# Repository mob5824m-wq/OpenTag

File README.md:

# OpenTag

OpenTag is an independent, open-source NFC handheld. `device/` contains the
ESP32-S3 firmware; `hardware/` contains the carrier PCB, enclosure CAD, wiring
guide, and parts list.

> OpenTag is not affiliated with or endorsed by Nintendo or any tag/device
> manufacturer. Amiibo is a trademark of Nintendo. **All amiibo tag data is
> user-supplied** — the project bundles, generates, and distributes none of
> it. Upload backups of tags you own, and only write to tags you are
> authorized to program.

## What it does

- **Write NDEF notes** — sync a text or HTTP(S) URL note over BLE and write it
  to a real NTAG215 (verified by read-back), from the device menu.
- **Emulate the NDEF note** — present the note as a virtual, read-only
  NTAG215; phones read it like any NDEF tag.
- **Amiibo library** — upload a `.zip` of your own NTAG215 `.bin` dumps
  through the web page or the **Android app**, browse them on the OLED, and
  tap a console with the dump's own 7-byte UID presented by the NFC emulator.
  **OpenTag emulates amiibo — that's the product**; bins show metadata and
  box art in the web page and app, matched by file name against a bundled
  932-entry amiibo database.
- **Android app** ([`android-app/`](android-app/)) — native Kotlin app
  (no dependencies) for BLE file dumping: pick `.bin` dumps or a `.zip` of
  them, upload to the device, browse the on-device library, and trigger
  emulation. Every merge to `main` auto-builds a fresh signed `.apk`
  (`app-v*` releases on the Releases page) — download and sideload it, no
  Android Studio needed.
- **OpenTag Mini** — a screenless, pocket-flatter variant of the same
  electronics: no OLED, no nav buttons, **no Bluetooth pairing PIN**
  (just-works pairing — it's keyed to your desk, not to a shared bench).
  Everything is driven from the Android app or the web page, which
  recognise the device and label it **Mini** with a matching button set;
  the single button handles battery chirps, travel mode and power.
- **Wireless charging (optional)** — a Qi receiver coil inside the back
  plate charges the OpenTag from any Qi pad through the existing TP4056
  (an engraved ring on the back marks the spot); with the optional charge
  -sense wire, a bolt icon on the OLED confirms the pad is coupled.
- **Tag backup (reader mode)** — from the device menu, tap any amiibo
  against the back window and the firmware reads, validates, and stores the
  dump in the library (named by the tag's UID; full 1024-byte images for
  V3/NTAG I²C tags). No phone needed.
- **Tag inspector** — the third menu item turns the OpenTag into a tag
  identifier: tap any tag on the back window and the OLED shows its UID,
  chip type (NTAG213/215/216, MIFARE UL…) and any NDEF text/URL payload.
  Nothing is written; it's the safe "what is this tag?" answer.
- **Battery gauge + low-battery protection (optional)** — a 100k/100k
  divider on B+ feeds GPIO4; the header shows a charge percentage, turns
  red at/below 15 %, warns once at 3.35 V and (with the divider fitted)
  powers the device off cleanly if the cell sags below 3.25 V for 30 s.
- **BLE pairing with a PIN** — the first phone to connect runs the standard
  numeric-comparison pairing flow: the OLED shows a random 6-digit code,
  the phone asks to confirm it, and the bond is stored (a failed exchange
  is disconnected immediately). Re-pair by deleting the bond on the phone.
- **USB drive mode (read-only)** — docked in the menu, the DevKit's USB-C
  port enumerates as a USB mass-storage drive exposing a read-only snapshot
  of the amiibo library (plus a README) — drag bins off the device with no
  app at all. Loading new dumps still goes over BLE (the drive is a
  snapshot; OK/BACK ejects it).
- **Wi-Fi OTA updates (optional)** — provision Wi-Fi credentials over BLE
  (`WIFI:<ssid>|<pass>`), then trigger an update from the web page's
  Settings (or `OTA:START`): the device fetches the latest GitHub release,
  flashes only the app partition and reboots — library and settings survive,
  exactly like the wired one-command updater.
- **Piezo feedback (optional)** — a passive buzzer on GPIO5 chirps on tag
  backup, verified writes, pairing and the low-battery warning. Unwired,
  the device stays silent, as before.
- **One-command firmware updates** ([`tools/update_opentag.py`](tools/update_opentag.py))
  — plug the OpenTag into a computer and run the script: it downloads the
  latest firmware release from GitHub (CI builds and attaches it on every
  `v*` tag) and flashes **only the app partition** — your amiibo library,
  settings, and note survive every update.
- **Advanced: write amiibo to physical NTAG215 tags (TagMo-style)** — with
  your own `unfixed-info.bin` / `locked-secret.bin` key files uploaded over
  BLE, the device can re-sign a dump for a blank tag's own UID, write and
  verify it, and optionally lock it (irreversible, long-press confirm on the
  device). Emulation needs none of this; the flow remains available behind a
  long-press in the device library.
- **BLE sync** — Web Bluetooth page with note management, .zip upload, device
  library listing with metadata + box art, remote emulate/delete.
- **Web preview of the device UI** ([`device/web-preview/`](device/web-preview/))
  — a browser simulation of the OLED interface (every screen, color, and
  pixel position ported from `drawScreen()`) with working buttons and
  long-press, for UI testing with no hardware attached.

## Set up your OpenTag

Three ways in, depending on what's on your desk. **A** needs nothing, **B**
is a working device on a bench in an afternoon, **C** is the finished
handheld.

### A · No hardware — try the interface (1 minute)

Open [`device/web-preview/index.html`](device/web-preview/index.html) in any
browser: a pixel-faithful simulation of the OLED menu with working buttons
and long-press — every screen the real device shows, nothing to install.

### B · Bench build — a working device today

Parts: **ESP32-S3-DevKitC-1** (16 MB flash), **PN532Killer**, **1.3"
SSD1351 OLED** (7-pin SPI), 4 × tactile buttons, Dupont jumpers, USB-C
cable. No PCB, no soldering — USB powers the whole bench setup.

1. Install [PlatformIO](https://platformio.org/) (VS Code extension or
   `pip install platformio`).
2. Flash the firmware and the library filesystem:
   ```sh
   cd device
   pio run -e opentag_s3 -t upload      # firmware (app partition only)
   pio run -e opentag_s3 -t uploadfs    # LittleFS: on-device amiibo storage
   ```
3. Wire the modules (full map and rationale in
   [`docs/HARDWARE.md`](docs/HARDWARE.md)):

   | Connection | DevKit pin (GPIO) | Module side |
   |---|---|---|
   | OLED VCC / GND | J1-1 (3V3) / GND | VCC / GND |
   | OLED SCK / MOSI | J1-18 (12) / J1-17 (11) | SCL / SDA |
   | OLED CS / DC / RST | J1-16 (10) / J1-15 (9) / J1-12 (8) | CS / DC / RES |
   | Killer 3V3 / GND (J4) | J1-2 (3V3) / GND | VCC / GND |
   | Killer RX / TX (J4) | J1-10 TX (17) / J1-11 RX (18) | crossed: TX → RX |
   | Buttons UP / DOWN / OK / BACK | J3-6 (42) / J3-5 (2) / J3-4 (1) / J1-19 (13) | one leg each; other legs to GND |

4. Plug in USB — the OLED shows the menu within a couple of seconds. Only
   the NFC actions need the Killer attached; trying one without it shows
   **PN532Killer absent** on screen. Wire it in and the whole menu is live.
5. Serve the sync page. Web Bluetooth only runs on a secure origin
   (localhost or HTTPS) — **double-clicking the file is not enough**:
   ```sh
   cd device/web-sync
   python3 -m http.server 8000        # then open http://localhost:8000
   ```
6. In Chrome or Edge: **Connect over BLE** (the device shows up as
   *OpenTag*) → pick a `.zip` of your own NTAG215 `.bin` dumps → they land
   in the on-device library with names and box art. Browse on the OLED,
   press OK on one, and tap your console.

Optional extras on the same hardware: send a text/URL **NDEF note** from the
sync page (the device menu can write it to a blank NTAG215 or emulate it —
a good first test of the tag pipeline), and — only if you write amiibo to
physical tags — upload your `unfixed-info.bin` / `locked-secret.bin` key
files. Emulation needs neither.

### C · Full handheld

1. **Order the PCB** — upload
   [`hardware/pcb/gerbers/opentag-gerbers.zip`](hardware/pcb/gerbers/) to any
   fab (JLCPCB, PCBWay, …). The zip is complete and machine-verified by its
   generator.
2. **Print the shell** — [`hardware/cad/stl/`](hardware/cad/stl/): front
   shell, back plate, 4 button caps (PLA/PETG, no supports needed).
3. **Assemble** per [`docs/WIRING.md`](docs/WIRING.md);
   parts and budget in [`docs/BOM.md`](docs/BOM.md) (≈ $72–102
   complete). Print [`docs/opentag-user-guide.pdf`](docs/opentag-user-guide.pdf)
   as the user manual.
4. The device is identical to the bench build — continue from step 5 in
   path **B**.

Updating an assembled device later never touches your library:
`python tools/update_opentag.py` flashes only the app partition
([details](#updating-the-firmware-keeps-your-amiibos)).

### D · OpenTag Mini (screenless)

The same electronics and BLE protocol with the screen and nav buttons
removed: **one button, a chirp, and the app or web page for everything.**
No OLED, no carrier PCB — the DevKitC and the three modules mount straight
into printed trays, and the shell closes at 83.6 × 93.6 × 16.3 mm
(31 % shorter and 44 % thinner than the handheld, and it skips the numeric
pairing PIN entirely). The Android app and web page detect it on connect
(`INFO` → `mini`) and swap in the Mini control set — emulate, backup,
inspect, write note — same library, same keys, same Wi-Fi/OTA.

1. **Print the Mini shell** —
   [`hardware/cad/stl/opentag_mini_*.stl`](hardware/cad/stl/): front
   shell, back plate, **1** button cap (no desk stand — the Mini has no
   reading pose to hold).
2. **Assemble point-to-point** per
   [`docs/WIRING.md`](docs/WIRING.md#opentag-mini-variant) — no PCB, no
   soldering beyond tinning the module pads: DevKitC + Killer + TP4056 +
   MT3608 + LiPo + one tactile switch, parts in
   [`docs/BOM.md`](docs/BOM.md#opentag-mini-delta).
3. **Flash the Mini firmware** (same library filesystem as the handheld):
   ```sh
   cd device
   pio run -e opentag_mini -t upload
   pio run -e opentag_mini -t uploadfs
   ```
4. Pair from the app or web page — the device shows up as **OpenTag Mini**
   and connects with no PIN prompt. The single button: **short press**
   chirps the battery level (one chirp per 20 %), **triple press** toggles
   travel mode, **hold 1.5 s** powers off (short press wakes).

ESP32-S3-DevKitC-1 + **PN532Killer** (ST25R3916-class NFC emulator; the
classic PN532 cannot present the 7-byte, signature-bound UIDs amiibo relies
on) + SSD1351 OLED + four buttons (UP / DOWN / OK / BACK) + LiPo power
(TP4056 + MT3608). The NFC
board talks HSU UART to the ESP32; a 540-byte page image per tag is all the
firmware pushes. The SW-corner tab is a lanyard / keyring loop (4.2 mm bore,
continuous through the front/back seam). See [`docs/HARDWARE.md`](docs/HARDWARE.md) for the full
interface map and [`hardware/`](hardware/) for:

| File | Contents |
|---|---|
| `hardware/pcb/opentag-carrier.kicad_pcb` | 90 × 60 mm 2-layer carrier, all through-hole |
| `hardware/pcb/generate_carrier_pcb.py` | Regenerates the PCB and self-checks connectivity + clearance |
| `hardware/pcb/gerbers/` | Fab-ready Gerber set + Excellon drill + `opentag-gerbers.zip` — the generator writes them and re-parses them to verify against the model |
| `docs/WIRING.md` | Assembly, power chain, signal map, bring-up |
| `docs/HARDWARE.md` | Device interface baseline — the contract the firmware implements (buttons, display, NFC, power, USB) |
| `hardware/cad/opentag_shell.cad` | Parametric 2-part handheld shell + button caps, with the ⚡-marked USB-C charge port on the west wall and a lanyard loop tab on the SW corner (OpenSCAD source; `.cad` is the project's extension) |
| `hardware/cad/opentag_mini_shell.cad` | Parametric 2-part **Mini** shell + its single button cap — screenless variant, 83.6 × 93.6 × 16.3 mm, module trays instead of a carrier PCB, same west USB / east charge-slot layout and lanyard loop |
| `hardware/cad/stl/*.stl` | Print-ready binary STLs: handheld front shell, back plate, button cap (print 4) and optional desk stand; Mini front shell, back plate, button cap (print 1) |
| `tools/cad_to_stl.py` | Regenerates the STLs from the `.cad` without OpenSCAD (`pip install trimesh manifold3d scipy rtree`) and self-checks watertightness, features and front/back fit |
| `tools/cad_mini_to_stl.py` | Same idea for the Mini shell: parses `opentag_mini_shell.cad`, rebuilds all three parts, and self-checks volumes, features and front/back fit || `docs/BOM.md` | Parts list and budget (≈ $72–102) |
| `docs/opentag-user-guide.pdf` | The printed instruction booklet — 16 A5 pages covering charging, the desk stand, buttons, the library, V3 amiibo, BLE sync, writes, USB drive, the Mini variant and troubleshooting |
| `docs/ANDROID-APP.md` | Android companion app — features, BLE protocol, releases |
| `docs/SIGNING-KEY.md` | The committed APK signing key: why it's public, and how to swap in a private one |
| `tools/make_booklet.py` | Regenerates the booklet (`pip install fpdf2`); its cover art is parsed straight from the shell's own wordmark font and bolt icon |

## Updating the firmware (keeps your amiibos)

Push a `v*` tag and CI (`.github/workflows/firmware.yml`) builds **both**
firmwares — the handheld and the Mini — and attaches them to a GitHub
release as `opentag-firmware-<tag>.bin` and
`opentag-mini-firmware-<tag>.bin`. Then, on any computer with Python:

```sh
pip install esptool
python tools/update_opentag.py            # auto port, latest release (handheld)
python tools/update_opentag.py --mini     # the Mini variant
python tools/update_opentag.py --tag v1.2 # a specific release
python tools/update_opentag.py --bin firmware.bin --port COM5
```

The script reads the app partition offset from `device/partitions_16mb.csv`
and flashes **only that partition** — the LittleFS amiibo library, NVS
settings, and pending note are never touched. If no release asset exists it
falls back to building locally with `pio run`.

## Android app

Open [`android-app/`](android-app/) in Android Studio and run — see
[`docs/ANDROID-APP.md`](docs/ANDROID-APP.md). Platform
APIs only, no dependencies; minSdk 23.

## Tests and gates (host-native, no hardware)

The firmware build commands live in [Setup B](#b--bench-build--a-working-device-today).
Everything below runs on any machine with `g++` — no toolchain download, no
device attached.

Unit tests:

```sh
cd device/test
g++ -std=c++11 -Wall -Wextra -pedantic -I ../src test_ntag215_emu.cpp -o t1 && ./t1
g++ -std=c++11 -Wall -Wextra -pedantic -I host_stubs -I ../src test_pn532_uart.cpp -o t2 && ./t2
g++ -std=c++11 -Wall -Wextra -pedantic -I ../src test_amiibo_crypto.cpp -o t3 && ./t3
```

`test_amiibo_crypto` checks the signing pipeline byte-for-byte against
fixtures generated by the real
[amiitool](https://github.com/socram8888/amiitool) (MIT): its AES-128-CTR /
HMAC-SHA256 reference backends are themselves validated against FIPS-197,
FIPS-180-4 and RFC 4231 vectors first.

A firmware compile gate (syntax/type check of both firmwares against stub
Arduino/NimBLE/mbedtls headers — no toolchain download needed):

```sh
cd device/test
g++ -std=c++11 -Wall -Wextra -fsyntax-only -I host_stubs_main -I ../src ../src/main.cpp
g++ -std=c++11 -Wall -Wextra -fsyntax-only -I host_stubs_main -I ../src ../src/mini/main.cpp
```

CI runs all of the above plus full PlatformIO builds of **both** firmwares
on every PR or push touching `device/`
([firmware.yml](.github/workflows/firmware.yml)); only `v*` tag pushes
publish releases.

## Web sync

Open `device/web-sync/index.html` from a secure origin (HTTPS or localhost)
in Chrome/Edge, connect over BLE, then:

- queue a text/URL note and send it;
- choose a `.zip`, loose `.bin` dumps, or Flipper Zero `.nfc` files of your
  NTAG215 backups — the page unzips locally with the browser's native
  `DecompressionStream`, accepts any container layout (532/540/572 B,
  zero/newline-padded, N2 Elite 32-byte header, Flipper page lists), validates
  each dump (UID BCC, NTAG215 capability container), and copies the normalized
  540-byte image to the device in BLE chunks;
- every bin — local and on-device — shows **amiibo metadata and box art**,
  matched by file name (16-hex amiibo ID first, then a fuzzy name match)
  against `device/web-sync/amiibo-db.js`, a 932-entry database generated from
  the community AmiiboAPI project. The amiibo ID inside a retail dump is
  AES-encrypted, so file names are the reliable key. Images load from
  AmiiboAPI's CDN with a colored-initial fallback offline;
- list, emulate, or delete library entries on the device — emulation is the
  point; there is no per-amiibo write button;
- (advanced) upload your **amiibo signing keys** (`unfixed-info.bin` +
  `locked-secret.bin`, or one combined 160-byte retail file) if you also use
  the device's long-press physical-tag write flow.

Nothing is uploaded to any server; all processing happens in your browser.

### Amiibo metadata database

[`amiibo.json`](amiibo.json) (repository root) is the canonical,
human-editable database — 932 entries mapping each 16-hex amiibo ID to
`[name, amiiboSeries, type, gameSeries, releaseYear]`, generated from the
community [AmiiboAPI] database. Edit it, then run:

```sh
python tools/gen_amiibo_db.py   # -> web-sync/amiibo-db.js + android assets
```

[AmiiboAPI]: https://github.com/N3evin/AmiiboAPI

## Writing an amiibo to a physical tag

The write flow is the TagMo "WRITE TAG (AUTO)" sequence, re-implemented in
portable C++ from the MIT-licensed amiitool reference:

1. Read the blank tag's pages 0–3 (UID) and check `GET_VERSION` says NTAG215
   and the static lock bytes are still clear.
2. Decrypt the stored retail dump with keys derived from its own UID, patch
   the new tag's UID + BCC bytes in, re-encrypt and re-sign both HMACs.
3. Program pages 3–129, then the PWD (133) and PACK (134) pages derived from
   the new UID.
4. Read everything back and compare; finally `PWD_AUTH` must answer with the
   written PACK.
5. Optionally lock the tag (page 2 `xx xx 0F E0`, page 130 `01 00 0F 00`,
   page 131 `00 00 00 04` = AUTH0 4, page 132 `5F 00 00 00`) — **this is
   irreversible** and always requires the physical long-press confirmation on
   the device; it never happens remotely or by timeout.

Trigger it with `AMI:WRITE:<name>` over BLE or by long-pressing OK on a
library entry.

## Charging

Charge through the **USB-C port on the left side**, marked by the engraved
lightning bolt — the TP4056's charge LEDs peek through the same slot, and a
**light pipe** (a ~5 mm stub of 2.5 mm acrylic rod seated in the tray wall
just below the port) carries the charge LED's glow out through the west
face, so charging is visible with the case closed even in bright rooms. The
optional printed **desk stand**
([`hardware/cad/stl/opentag_desk_stand.stl`](hardware/cad/stl/opentag_desk_stand.stl))
holds the OpenTag leaning back at ~10° with the screen up and readable —
OLED end down at the front lip, the back resting on the stand's tall rear
panel. The chin's charge port ends up just behind the panel's top edge, so
the device still charges while docked with the cable dropped behind. The
stand's front brace carries an engraved **OPENTAG** wordmark, and the back
of the rear panel carries an engraved ring + bolt: stick a 5 V Qi
transmitter coil (≤ 40 mm, ferrite-backed) on that mark and the docked
device charges wirelessly — the mark is centred under the device's
receiver coil as far up the panel as it fits, but the ~10° lean still
offsets the coils, so expect a gentle charge rate rather than full power. **Wireless:** with
the optional Qi receiver coil fitted (see `docs/WIRING.md` — it sits
under the battery on the engraved ring, east of the tap halo), any Qi pad
charges the device through the same TP4056, and the bolt icon at the
top-right of the screen confirms the pad is coupled. Soft-off still draws a few mA
(the DevKitC regulator and boost stay alive), so use the side switch when
storing the device.

**On the Mini** the two ports live on opposite walls: the **DevKit's USB-C
on the west wall** (flashing, serial console, the read-only USB drive) and
the **TP4056 charge port on the east wall** — its USB-C jack and charge
LEDs sit in the east-wall slot with the light-pipe bore just beside it, so
charging is still visible with the case closed. There is no Qi option on
the Mini (the receiver coil would cover the Killer's tap window); charge
over USB-C.

## Device menu

`Amiibo library` (first — emulation is the main use, so the menu opens on
it) → `Backup tag` → `Inspect tag` → `BLE sync` → `Write NDEF note` →
`Emulate NDEF note` → `Clear NDEF note` → `USB drive` → `Factory reset`,
driven by UP/DOWN/OK with BACK to
cancel or exit. Holding UP or DOWN auto-repeats (first extra step after
450 ms, then accelerating), so long libraries scroll quickly. Emulation
starts on the PN532Killer's slot
0. **While an amiibo is emulating, UP/DOWN hot-swaps to the neighbouring
library entry without stopping** — each swap loads onto the next of the
Killer's 8 emulator slots (never rewriting the one being presented), so you
can tap console after console with different figures. OK/BACK stops the
emulation (any button stops NDEF-note emulation), as does a BLE `STOP`. In the library, short OK
emulates; long OK (1 s) is the advanced path that arms a write to a physical
tag. Long-pressing OK **at the menu** is soft power: a "Powering off" screen
appears (BACK cancels within ~0.7 s), then the OLED parks and the ESP32-S3
drops into deep sleep; holding OK for a full second wakes it back to the
menu. That's a convenience off, not a battery disconnect — the DevKitC's
regulator and the boost still draw a few mA asleep, so use the slide switch
for storage. **Auto-sleep:** after 3 minutes with no button, BLE or tag
activity the device powers off through the same flow (BACK still cancels
inside the window); mid-transfer BLE traffic resets the timer.

**Backup tag (reader mode):** the second menu item turns the OpenTag into a
reader — tap any amiibo (or other NTAG215) flat against the back window and
the firmware reads it, validates it (UID/BCC + capability container), and
saves a normalized 540-byte dump to the library under the tag's 7-byte UID
hex name (V3/NTAG I²C Plus tags save their full 1024-byte image instead).
An identical re-read says `Already saved` and just jumps to the entry; a
tag rewritten with different data but the same UID saves as `-2`, `-3`, …
BACK or OK leaves the reader screen.

**Inspect tag:** the third menu item identifies whatever you tap on the back
window — UID (hex), chip type from the capability container (NTAG213/215/216
or MIFARE UL, with the tag's byte capacity) and the first bytes of any NDEF
text/URL record, or `No NDEF data`. Tap again to re-scan another tag; it
never writes. Use it to sort blank tags from written ones, or to read what
an unknown sticker says before committing anything to it.

**USB drive (read-only snapshot):** menu item 8. The DevKit's own USB-C port
enumerates as a tiny USB mass-storage drive holding a *read-only snapshot*
of the amiibo library plus a README — copy bins off the device from any OS
with no app. It shares one USB port with the serial console, so the drive
replaces the console while docked (flash over the other USB-C port, or just
press OK/BACK to eject and get the console back). New dumps still go on
over BLE; the snapshot is rebuilt every time you dock.

**Battery telemetry:** with the optional 100k/100k divider fitted
(`docs/WIRING.md`), the header shows the cell's charge percentage
between the wordmark and the BLE indicator — grey normally, red at/below
15 %. Below 3.35 V the device warns once (`Battery low` + a chirp with the
piezo fitted); below 3.25 V sustained for 30 s it runs the clean
power-off flow to protect the cell (charging suspends the checks — the
terminal voltage rises while the TP4056 is active).

**Pairing & OTA:** on the **handheld**, the first BLE connection runs
numeric-comparison pairing: a random 6-digit PIN appears on the OLED, the
phone shows the same code, and the bond is stored. **The Mini pairs with
no PIN at all** (just-works, bond stored — screenless devices have nothing
to show a code on). **Wi-Fi updates:** in the web page's Settings (or
via BLE) send `WIFI:<ssid>|<pass>` once, then `OTA:START` (or the web page's
Update button) — the device joins Wi-Fi, fetches the newest GitHub release,
flashes only the app partition and reboots. Library, keys and settings
survive, same as the wired updater; BACK cancels mid-download.

**Travel mode:** hold BACK (1 s) at the menu to toggle. On, the device stops
BLE advertising completely — it won't appear in phone scans — while
everything else (emulation, buttons, auto-sleep) keeps working; `BLE sync`
while it's on says `Travel: BLE off`. The setting persists across reboots
and survives firmware updates. Use it anywhere you'd put a phone in
airplane mode.

**Random-UID re-sign (per amiibo):** hold BACK on a library entry to flag it
(an `R` badge appears). Every emulation or hot-swap of a flagged entry then
re-signs the dump for a fresh random UID with the on-device amiitool crypto,
so consoles treat it as a brand-new figure each time — needs your key files
loaded (`Random needs keys` says so otherwise), v2 dumps only, and the flag
persists as a zero-byte `.rnd` sidecar next to the dump.

**Factory reset:** the last menu item wipes the amiibo library (including
`.rnd` flags), the signing keys, and all settings (travel mode included)
back to as-built. The confirm screen requires **holding OK for ~1.2 s**;
any short press cancels, and the screen gives up on its own after 15 s.
There is no undo — re-load your dumps from the web page afterwards.

Preview the whole interface (buttons, long-press, every screen,
power off/on) in your
browser with [`device/web-preview/index.html`](device/web-preview/index.html).

**The Mini has no on-device menu** — every action above is reachable from
the Android app or the web page, which present the Mini-appropriate subset
(emulation, backup, inspect, random-UID, note write/emulate, library
management, USB drive, Wi-Fi/OTA). The single button covers what a
screenless device still needs locally: battery chirps, travel-mode toggle,
power off/wake, and cancelling an armed action (any press). Pairing is
just-works — no PIN is ever shown — and `INFO` reports the model so the
app and web page label the device **Mini** automatically.

## Scope notes

- **Amiibo signing keys are user-supplied at runtime and never bundled.**
  The re-signing code (`device/src/amiibo_crypto.h`) implements the publicly
  documented amiitool (MIT) algorithm; no Nintendo proprietary data ships in
  this repository. Uploaded keys live in the device's NVS (not encrypted at
  rest — the device is assumed personal, like a phone running TagMo).
- The NDEF-note emulation personality uses a random, persisted 7-byte UID.
- **Wireless charging is a hardware option**: a ⌀ ≤ 40 mm ferrite-backed Qi
  receiver coil (under the battery, on the engraved ring) feeds the TP4056
  through a second Schottky — see `docs/WIRING.md`. No firmware
  change needed; the optional 22 kΩ sense wire (GPIO21) lights the bolt.
- `docs/HARDWARE.md` documents the interface baseline; the PCB is
  self-checked by its generator but has not been manufactured in this repo —
  review it in KiCad before ordering.

## License

MIT License; see [`LICENSE`](LICENSE).

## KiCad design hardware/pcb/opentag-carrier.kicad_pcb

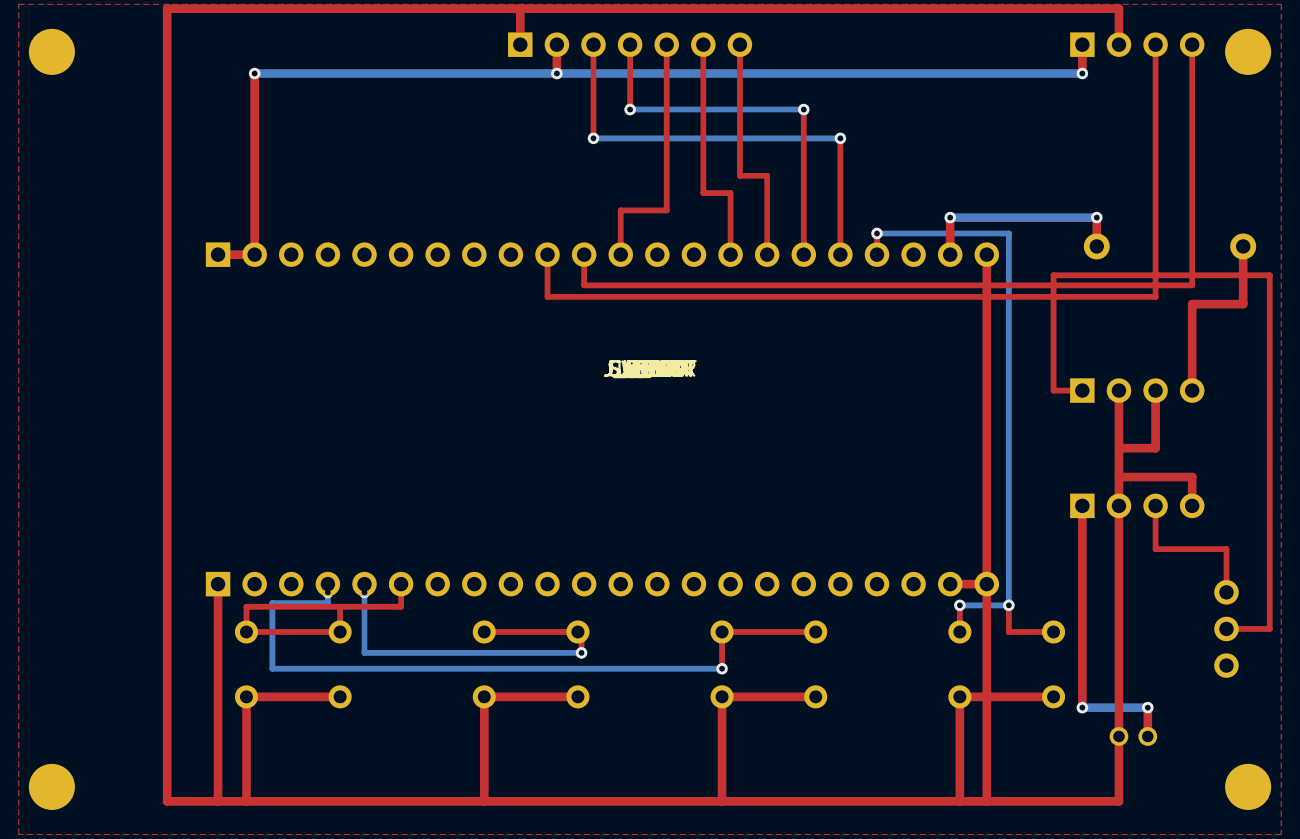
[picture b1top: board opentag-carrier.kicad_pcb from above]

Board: 2 copper layers, 10 parts (0 on the bottom side), 18 nets.

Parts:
D1: 1N5819; D_DO-41_10mm
J_BAT: LiPo 3.7V; JST_PH_2
J_BOOST: MT3608 IN+ IN- OUT- OUT+; PinHeader_1x04
J_CHG: TP4056 B+ B- OUT+ OUT-; PinHeader_1x04
J_DEVKIT: ESP32-S3-DevKitC-1; DevKitC1_socket
J_KILLER: PN532Killer J4; PinHeader_1x04
J_OLED: SSD1351 OLED; PinHeader_1x07
MH: MH; Misc
SW_BTN: SW_BTN; Misc
SW_PWR: POWER; Switch_SPDT_row

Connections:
+3V3: J_DEVKIT.J1-1, J_DEVKIT.J1-2, J_KILLER.1, J_OLED.2
+5V: D1.K, J_DEVKIT.J1-21
BOOST5: D1.A, J_BOOST.4
BTN_BACK: J_DEVKIT.J1-19, SW_BTN.25_1, SW_BTN.25_2
BTN_DOWN: J_DEVKIT.J3-5, SW_BTN.-8_1, SW_BTN.-8_2
BTN_OK: J_DEVKIT.J3-4, SW_BTN.8_1, SW_BTN.8_2
BTN_UP: J_DEVKIT.J3-6, SW_BTN.-25_1, SW_BTN.-25_2
ESP_RX: J_DEVKIT.J1-11, J_KILLER.4
ESP_TX: J_DEVKIT.J1-10, J_KILLER.3
GND: J_BAT.2, J_BOOST.2, J_BOOST.3, J_CHG.2, J_CHG.4, J_DEVKIT.J1-22, J_DEVKIT.J3-1, J_DEVKIT.J3-21, J_DEVKIT.J3-22, J_KILLER.2, J_OLED.1, SW_BTN.8_3, SW_BTN.8_4, SW_BTN.25_3, SW_BTN.25_4, SW_BTN.-8_3, SW_BTN.-8_4, SW_BTN.-25_3, SW_BTN.-25_4
OLED_CS: J_DEVKIT.J1-16, J_OLED.7
OLED_DC: J_DEVKIT.J1-15, J_OLED.6
OLED_MOSI: J_DEVKIT.J1-17, J_OLED.4
OLED_RST: J_DEVKIT.J1-12, J_OLED.5
OLED_SCK: J_DEVKIT.J1-18, J_OLED.3
SW1: J_CHG.3, SW_PWR.1
SW2: J_BOOST.1, SW_PWR.2
VBAT: J_BAT.1, J_CHG.1

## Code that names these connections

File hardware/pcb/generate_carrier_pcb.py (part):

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    ("J1", 12): NET["OLED_RST"], ("J1", 15): NET["OLED_DC"],
    ("J1", 16): NET["OLED_CS"], ("J1", 17): NET["OLED_MOSI"],
    ("J1", 18): NET["OLED_SCK"], ("J1", 21): NET["+5V"],
    ("J1", 19): NET["BTN_BACK"],   # GPIO13: BACK button (MISO pin reused)
    ("J3", 1): NET["GND"], ("J3", 21): NET["GND"], ("J3", 22): NET["GND"],
    ("J3", 4): NET["BTN_OK"], ("J3", 5): NET["BTN_DOWN"], ("J3", 6): NET["BTN_UP"],
}
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                      (28.0, -10.0), (28.0, BST_Y), (30.0, BST_Y)], TRACK_SIGNAL)

# --- UART to Killer -------------------------------------------------------------------------
route(NET["ESP_TX"], F, [dk_pin("J1", 10), (-7.11, -8.5), (35.08, -8.5),
                         (35.08, KIL_Y)], TRACK_SIGNAL)
route(NET["ESP_RX"], F, [dk_pin("J1", 11), (-4.57, -9.3), (37.62, -9.3),
                         (37.62, KIL_Y)], TRACK_SIGNAL)

# --- OLED bus (F channel for RST/DC/CS, B channel for SCK/MOSI) -------------------------------
route(NET["OLED_RST"], F, [dk_pin("J1", 12), (-2.03, -14.5), (1.16, -14.5),
                           (1.16, OLED_Y)], TRACK_SIGNAL)
route(NET["OLED_DC"], F, [dk_pin("J1", 15), (5.59, -15.7), (3.70, -15.7),
                          (3.70, OLED_Y)], TRACK_SIGNAL)
route(NET["OLED_CS"], F, [dk_pin("J1", 16), (8.13, -16.9), (6.24, -16.9),
                          (6.24, OLED_Y)], TRACK_SIGNAL)
route(NET["OLED_SCK"], F, [dk_pin("J1", 18), (13.21, -19.5)], TRACK_SIGNAL)
via(NET["OLED_SCK"], 13.21, -19.5)
route(NET["OLED_SCK"], B, [(13.21, -19.5), (-3.92, -19.5)], TRACK_SIGNAL)
via(NET["OLED_SCK"], -3.92, -19.5)
route(NET["OLED_SCK"], F, [(-3.92, -19.5), (-3.92, OLED_Y)], TRACK_SIGNAL)
route(NET["OLED_MOSI"], F, [dk_pin("J1", 17), (10.67, -21.5)], TRACK_SIGNAL)
via(NET["OLED_MOSI"], 10.67, -21.5)
route(NET["OLED_MOSI"], B, [(10.67, -21.5), (-1.38, -21.5)], TRACK_SIGNAL)
via(NET["OLED_MOSI"], -1.38, -21.5)
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# stacked lanes y = 16.2 / 17.3 between the signal and GND pin rows. BACK
# arrives from the north row (J1-19): it hops to the back layer, crosses the
# socket's east end (past J1-22/J3-22) and comes back up between the rows.
route(NET["BTN_UP"], F, [dk_pin("J3", 6), (-17.27, 13.0), (-28.0, 13.0)])
route(NET["BTN_UP"], F, [(-28.0, 13.0), (-28.0, 14.75)])
route(NET["BTN_UP"], F, [(-21.5, 13.0), (-21.5, 14.75)])
route(NET["BTN_UP"], F, [(-28.0, 14.75), (-21.5, 14.75)])
route(NET["BTN_DOWN"], F, [dk_pin("J3", 5), (-19.81, 12.0)])
via(NET["BTN_DOWN"], -19.81, 12.0)
route(NET["BTN_DOWN"], B, [(-19.81, 12.0), (-19.81, 16.2), (-4.75, 16.2)])
via(NET["BTN_DOWN"], -4.75, 16.2)
route(NET["BTN_DOWN"], F, [(-4.75, 16.2), (-4.75, 14.75)])
route(NET["BTN_DOWN"], F, [(-4.75, 14.75), (-11.5, 14.75)])
route(NET["BTN_OK"], F, [dk_pin("J3", 4), (-22.35, 12.0)])
via(NET["BTN_OK"], -22.35, 12.0)
route(NET["BTN_OK"], B, [(-22.35, 12.0), (-22.35, 12.75), (-26.2, 12.75),
                         (-26.2, 17.3), (5.0, 17.3)])
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route(NET["BTN_OK"], F, [(5.0, 14.75), (11.5, 14.75)])
# BACK's west signal pin needs its own via: the J3-22 GND link at x = 23.37
# runs between the two BACK pins all the way to the GND backbone.
route(NET["BTN_BACK"], F, [dk_pin("J1", 19), (15.75, -12.9)])
via(NET["BTN_BACK"], 15.75, -12.9)
route(NET["BTN_BACK"], B, [(15.75, -12.9), (24.9, -12.9), (24.9, 12.9)])
via(NET["BTN_BACK"], 24.9, 12.9)
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

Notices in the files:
hardware/pcb/generate_carrier_pcb.py:
render. Source: Adafruit-GFX-Library glcdfont.c (BSD license).
